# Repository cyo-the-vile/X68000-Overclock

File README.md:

# X68000 Overclock
 Simple Circuit for overclocking X68000 computers

X68000 Simple Overclock Circuit that requires a 4.7K pullup resistor, a DIP8 Socket, and a SN74F157 in SOIC package.

Please report clocks and models that are successful.

For PRO, for 15MHZ performance, Use a 60mhz oscillator.   PRO model will also require a seperate 5mhz oscillator installed near DMAC controller.  
For XVI, for 24mhz performance, use a 48mhz oscillator

It is recommended to install the clock switch in the position where the FG screw is on the rear of the computer case.  
This will ensure minimal case cutting and case modification.

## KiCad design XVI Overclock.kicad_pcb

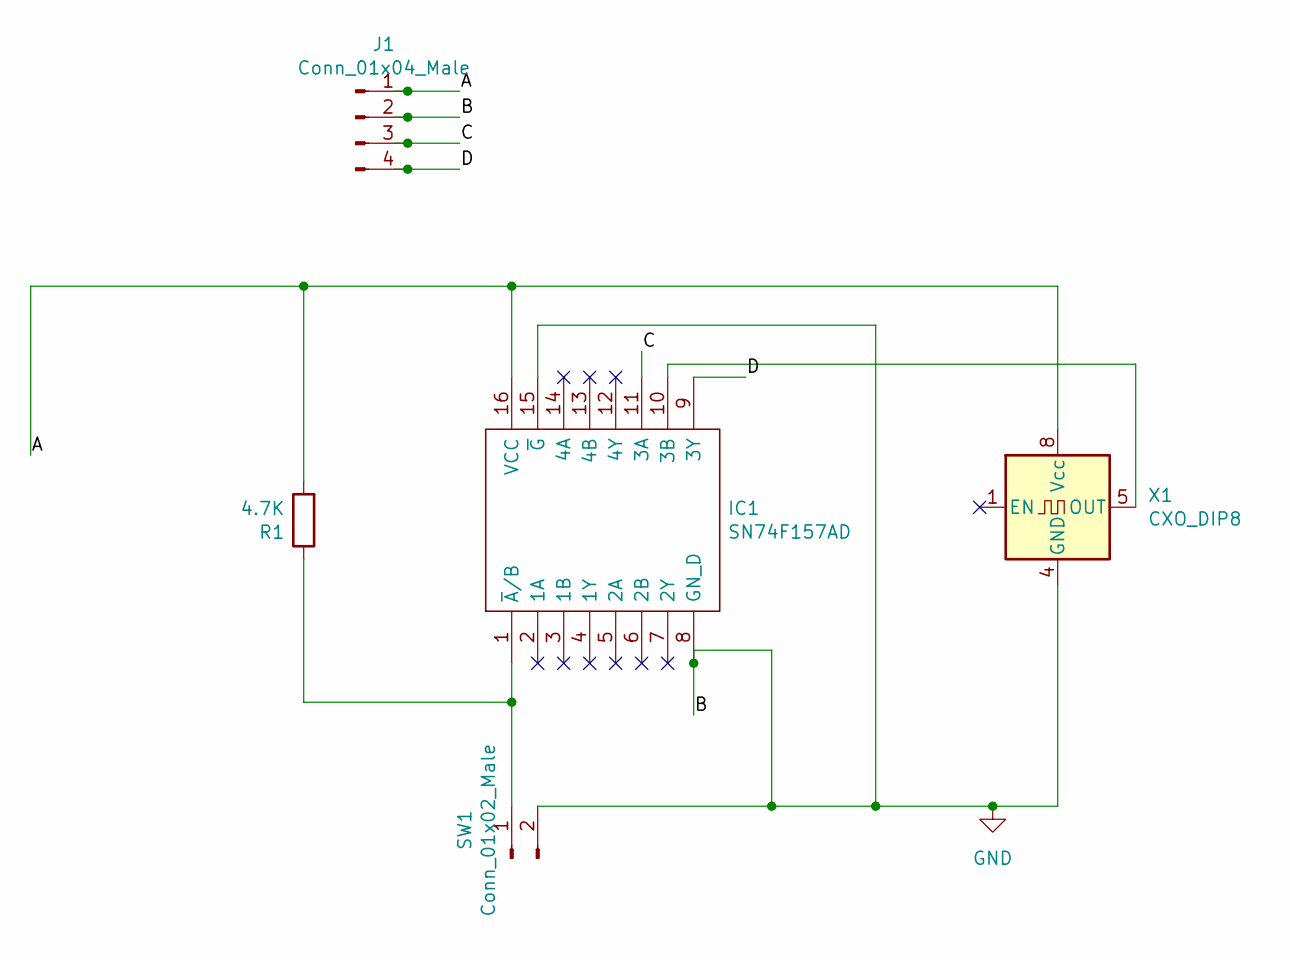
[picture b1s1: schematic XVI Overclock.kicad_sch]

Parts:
IC1: SN74F157AD; SOP-16_3.9x9.9mm_P1.27mm; Manufacturer_Part_Number SN74F157AD; Mouser Part Number 595-SN74F157AD
J1: Conn_01x04_Male; PinSocket_1x04_P2.54mm_Vertical
R1: 4.7K; R_Axial_DIN0207_L6.3mm_D2.5mm_P10.16mm_Horizontal
SW1: Conn_01x02_Male; PinSocket_1x02_P2.54mm_Vertical
X1: CXO_DIP8; Oscillator_DIP-8

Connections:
/A: IC1.16 (VCC), J1.1, R1.2, X1.8 (Vcc)
/B: IC1.8 (GN_D), IC1.15 (~G), J1.2, SW1.2, X1.4 (GND)
/C: IC1.11 (3A), J1.3
/D: IC1.9 (3Y), J1.4
unnamed: IC1.1 (~A/B), R1.1, SW1.1
unnamed: IC1.10 (3B), X1.5 (OUT)

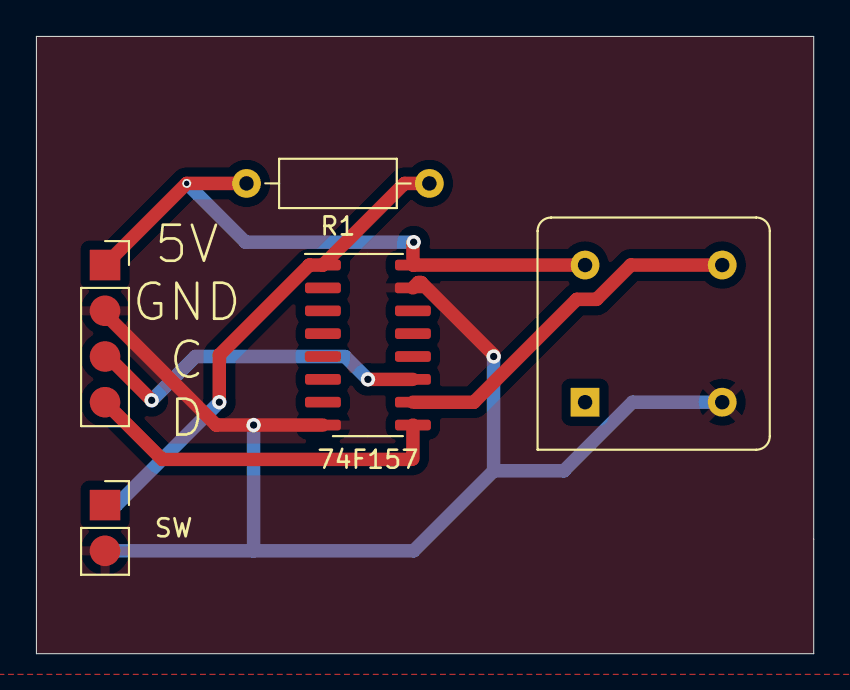
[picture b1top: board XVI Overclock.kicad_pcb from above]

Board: 2 copper layers, 43.2 x 34.3 mm, 5 parts (0 on the bottom side), 6 nets.

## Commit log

2024-12-07 Init
    Init
